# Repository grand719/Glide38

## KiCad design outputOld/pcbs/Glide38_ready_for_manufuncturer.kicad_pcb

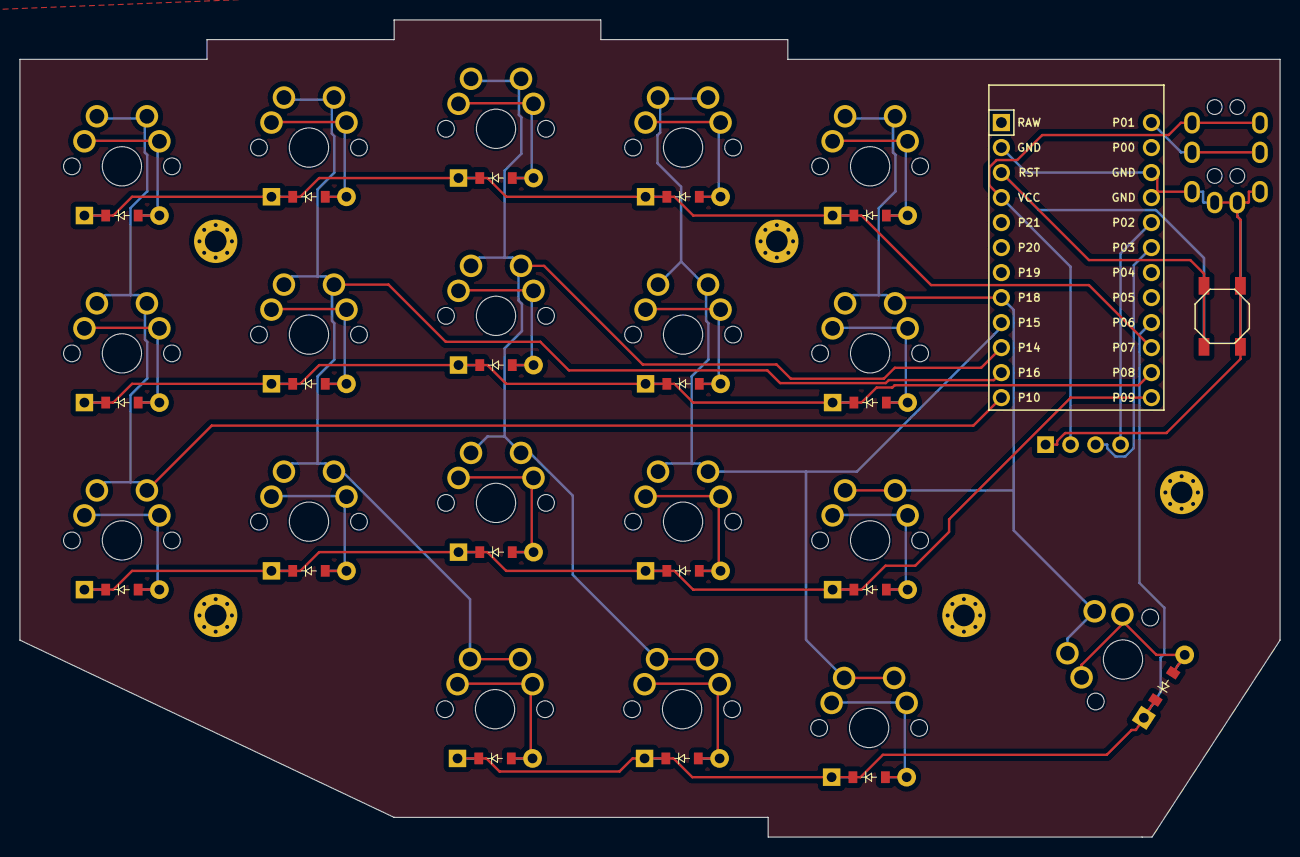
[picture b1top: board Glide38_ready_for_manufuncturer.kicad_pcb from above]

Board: 2 copper layers, 128.0 x 83.0 mm, 48 parts (0 on the bottom side), 34 nets.

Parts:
B1, B2: SW_TACT_ALPS_SKQGABE010
D1, D2, D3, D4, D5, D6, D7, D8, D9, D10, D11, D12, D13, D14, D15, D16, D17, D18, D19: ComboDiode
MCU1: ProMicro
OLED1: OLED; OLED_headers
S1, S2, S3, S4, S5, S6, S7, S8, S9, S10, S11, S12, S13, S14, S15, S16, S17, S18, S19: MX
TRRS1: TRRS-PJ-320A-dual
_1, _2, _3, _4, _5: MountingHole_2.2mm_M2_Pad_Via

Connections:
GND: B1.2, B2.2, MCU1.2, MCU1.15, MCU1.16, OLED1.1, TRRS1.1, TRRS1.2
P1: MCU1.13, TRRS1.3
P2: MCU1.17, OLED1.4
P3: MCU1.18, OLED1.3
P6: D16.1, D17.1, D18.1, D19.1, MCU1.21
P7: D3.1, D6.1, D9.1, D12.1, D15.1, MCU1.22
P8: D2.1, D5.1, D8.1, D11.1, D14.1, MCU1.23
P9: D1.1, D4.1, D7.1, D10.1, D13.1, MCU1.24
P10: MCU1.12, S1.1, S2.1, S3.1
P14: MCU1.10, S7.1, S8.1, S9.1, S17.1
P15: MCU1.9, S10.1, S11.1, S12.1, S18.1
P16: MCU1.11, S4.1, S5.1, S6.1, S16.1
P18: MCU1.8, S13.1, S14.1, S15.1, S19.1
RST: B1.1, B2.1, MCU1.3
VCC: MCU1.4, OLED1.2, TRRS1.4
alt_cluster: D16.2, S16.2
ctrl_cluster: D17.2, S17.2
index_bottom: D11.2, S11.2
index_home: D12.2, S12.2
index_mod: D10.2, S10.2
inner_bottom: D14.2, S14.2
inner_home: D15.2, S15.2
inner_mod: D13.2, S13.2
layer_cluster: D18.2, S18.2
middle_bottom: D8.2, S8.2
middle_home: D9.2, S9.2
middle_mod: D7.2, S7.2
outer_bottom: D2.2, S2.2
outer_home: D3.2, S3.2
outer_mod: D1.2, S1.2
ring_bottom: D5.2, S5.2
ring_home: D6.2, S6.2
ring_mod: D4.2, S4.2
space_cluster: D19.2, S19.2

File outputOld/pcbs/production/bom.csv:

Designator,Footprint,Quantity,Value,LCSC Part #
"B1, B2",SW_TACT_ALPS_SKQGABE010,2,,
"D1, D10, D11, D12, D13, D14, D15, D16, D17, D18, D19, D2, D3, D4, D5, D6, D7, D8, D9",ComboDiode,19,,
MCU1,ProMicro,1,,
OLED1,OLED_headers,1,OLED,
"S1, S10, S11, S12, S13, S14, S15, S16, S17, S18, S19, S2, S3, S4, S5, S6, S7, S8, S9",MX,19,,
TRRS1,TRRS-PJ-320A-dual,1,TRRS-PJ-320A-dual,
"_1, _2, _3, _4, _5",MountingHole_2.2mm_M2_Pad_Via,5,,

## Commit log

2024-05-12 Remove files
2024-05-12 Add 3d models
2024-05-12 Move gerber file
